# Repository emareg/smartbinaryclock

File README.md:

# smartbinaryclock
binary clock with several sensors

### Features:
* hour, minute, second
* day, month, year
* alarm clock

### Sensors:
* temperature
* brightness
* (barometer)

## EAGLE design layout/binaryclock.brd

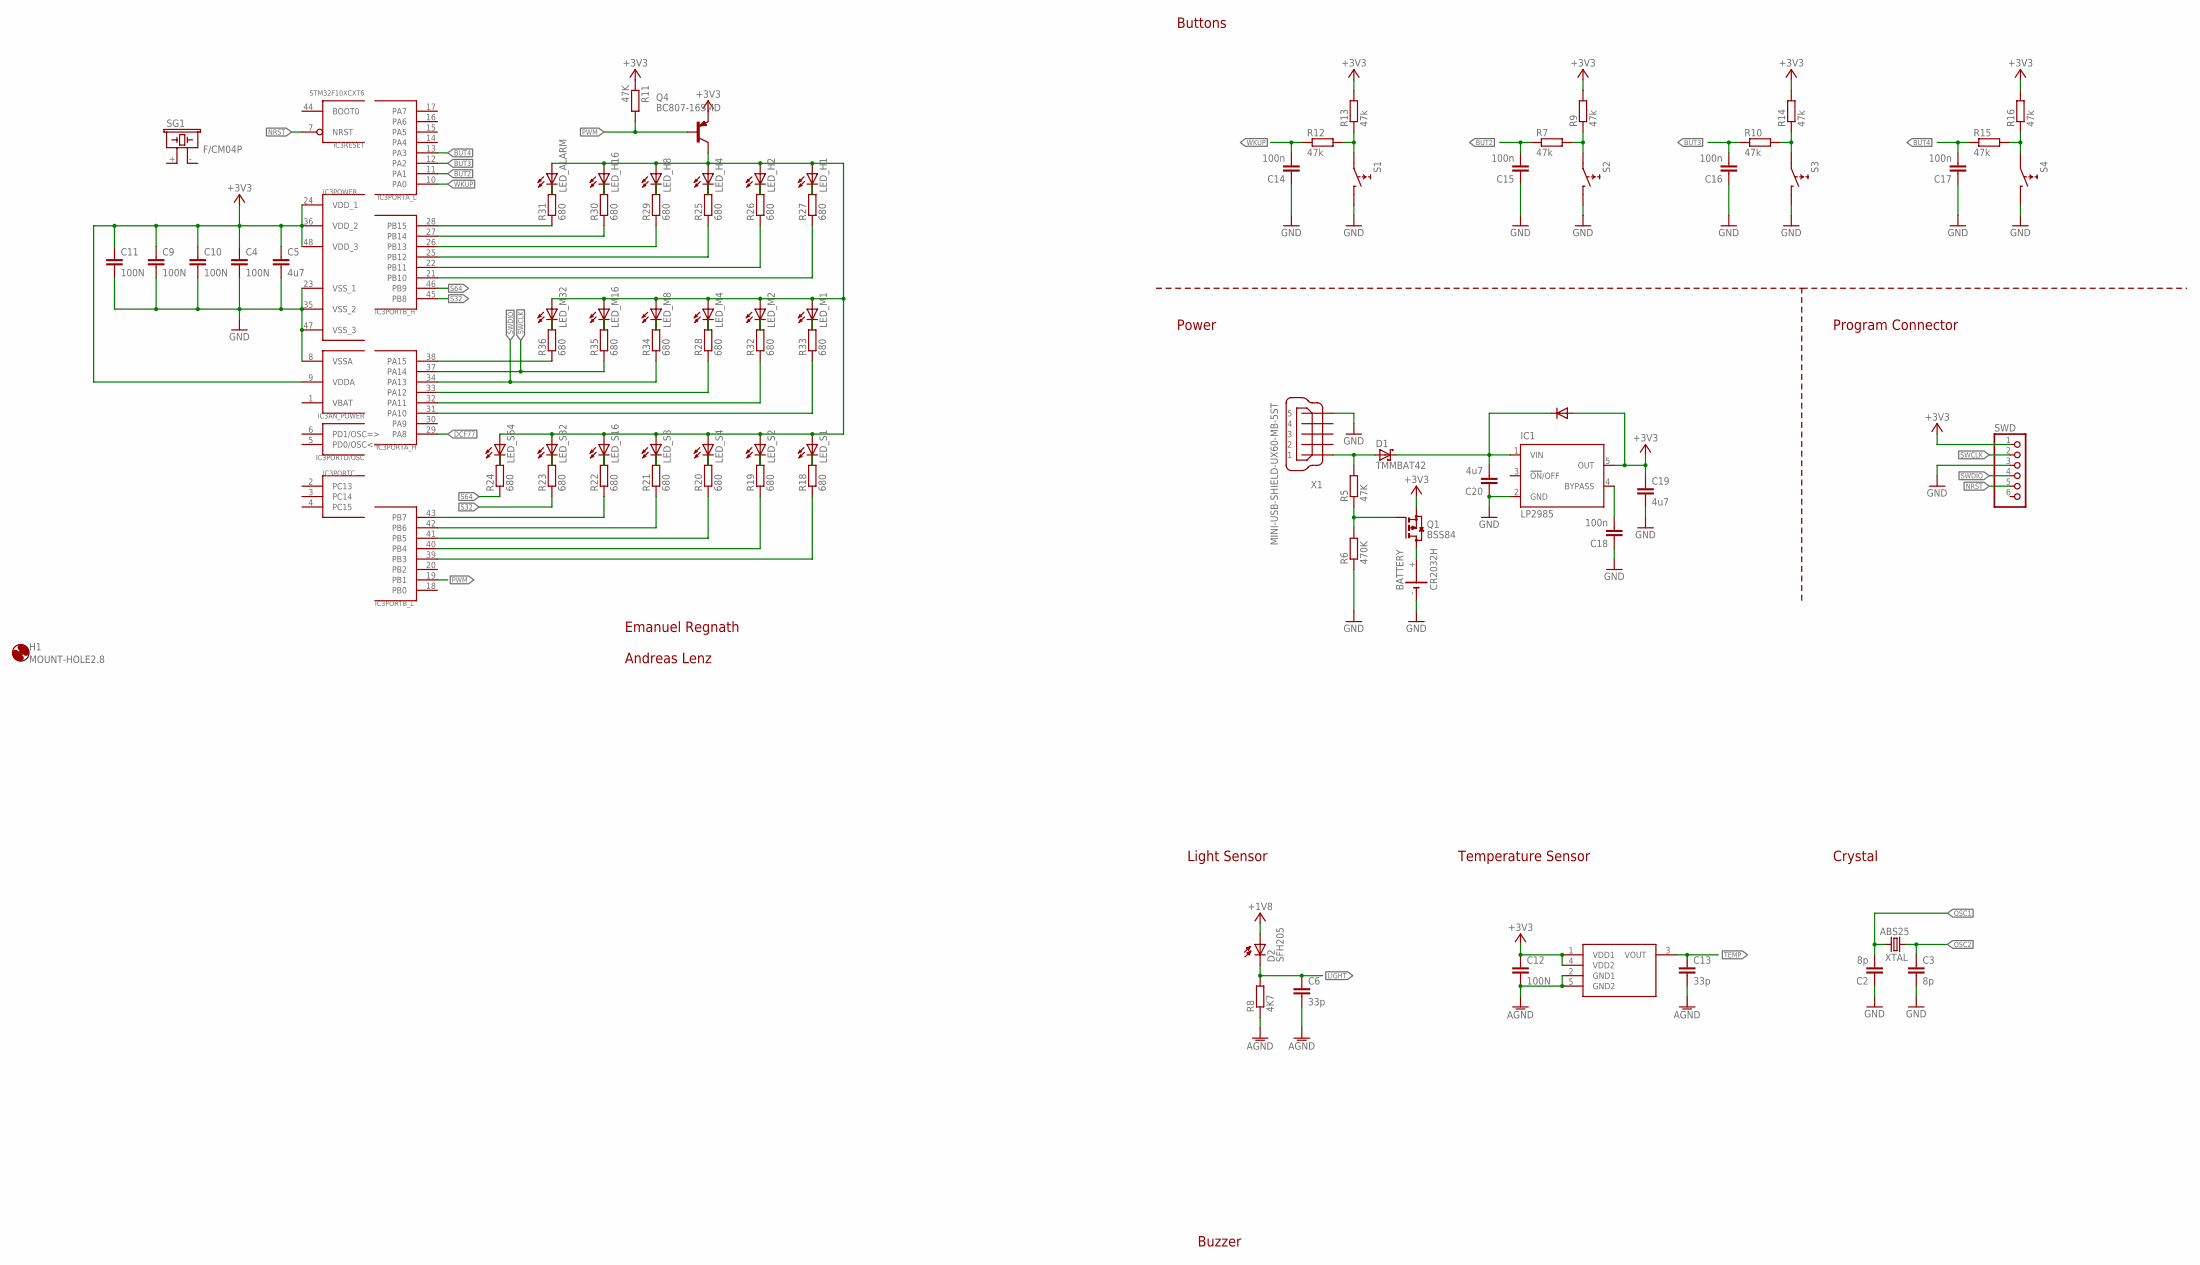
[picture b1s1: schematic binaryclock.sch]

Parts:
BATTERY: CR2032H
BLA: LMT85; DCK_R-PDSO-G5
C2, C3: 8p; C0805K
C4, C9, C10, C11, C12: 100N; C0603
C5, C19, C20: 4u7; C0805
C6, C13: 33p; C0603
C14, C15, C16, C17, C18: 100n; C0603K
D1: TMMBAT42; SOD80
D2: SFH205
H1: MOUNT-HOLE2.8; 2,8
IC1: LP2985; SOT23-5
IC3: STM32F10XCXT6; TQFP48
LED_ALARM: LEDSML0603; SML0603
LED_H1, LED_H2, LED_H4, LED_H8, LED_H16: LEDSML0603; SML0603
LED_M1, LED_M2, LED_M4, LED_M8, LED_M16, LED_M32: LEDSML0603; SML0603
LED_S1, LED_S2, LED_S4, LED_S8, LED_S16, LED_S32, LED_S64: LEDSML0603; SML0603
Q1: BSS84; SOT23
Q4: BC807-16SMD; SOT23-BEC
R5, R11: 47K; R0805
R6: 470K; R0805
R7, R9, R10, R12, R13, R14, R15, R16: 47k; M2012
R8: 4K7; R0603
R18, R19, R20, R21, R22, R23, R24, R25, R26, R27, R28, R29, R30, R31, R32, R33, R34, R35, R36: 680; R0603
S1, S2, S3, S4: SWITCH1
SG1: F/CM04P
SWD: PINHD-1X6; 1X06
X1: MINI-USB-SHIELD-UX60-MB-5ST; UX60-MB-5ST
XTAL: ABS25

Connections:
+1V8: D2.A
+3V3: BLA.1 (VDD1), BLA.4 (VDD2), C4.1, C5.1, C9.1, C10.1, C11.1, C12.1, C19.1, IC1.5 (OUT), IC3.9 (VDDA), IC3.24 (VDD_1), IC3.36 (VDD_2), IC3.48 (VDD_3), Q1.2 (S), Q4.E, R9.2, R11.1, R13.2, R14.2, R16.2, SWD.1
AGND: BLA.2 (GND1), BLA.5 (GND2), C6.2, C12.2, C13.2, R8.1
BUT2: C15.2, IC3.11 (PA1), R7.1
BUT3: C16.2, IC3.12 (PA2), R10.1
BUT4: C17.2, IC3.13 (PA3), R15.1
DCF77: IC3.29 (PA8)
GND: BATTERY.-, C2.1, C3.2, C4.2, C5.2, C9.2, C10.2, C11.2, C14.1, C15.1, C16.1, C17.1, C18.1, C19.2, C20.1, IC1.2 (GND), IC3.8 (VSSA), IC3.23 (VSS_1), IC3.35 (VSS_2), IC3.47 (VSS_3), R6.1, S1.P$2 (1), S2.P$2 (1), S3.P$2 (1), S4.P$2 (1), SWD.3, X1.5
LIGHT: C6.1, D2.K (C), R8.2
unnamed: BATTERY.+, Q1.3 (D)
unnamed: Q1.1 (G), R5.1, R6.2
unnamed: C20.2, D1.1 (C), IC1.1 (VIN)
unnamed: R12.2, R13.1, S1.P$1 (0)
unnamed: D1.2 (A), R5.2, X1.1
unnamed: IC3.38 (PA15), R36.1
unnamed: IC3.39 (PB3), R18.1
unnamed: LED_ALARM.A, LED_H1.A, LED_H2.A, LED_H4.A, LED_H8.A, LED_H16.A, LED_M1.A, LED_M2.A, LED_M4.A, LED_M8.A, LED_M16.A, LED_M32.A, LED_S1.A, LED_S2.A, LED_S4.A, LED_S8.A, LED_S16.A, LED_S32.A, LED_S64.A, Q4.C
unnamed: R7.2, R9.1, S2.P$1 (0)
unnamed: R10.2, R14.1, S3.P$1 (0)
unnamed: R15.2, R16.1, S4.P$1 (0)
unnamed: C18.2, IC1.4 (BYPASS)
unnamed: LED_M8.C, R34.2
unnamed: LED_S1.C, R18.2
unnamed: IC3.40 (PB4), R19.1
unnamed: LED_S8.C, R21.2
unnamed: IC3.41 (PB5), R20.1
unnamed: IC3.42 (PB6), R21.1
unnamed: LED_H8.C, R29.2
unnamed: LED_S2.C, R19.2
unnamed: LED_S4.C, R20.2
unnamed: IC3.33 (PA12), R28.1
unnamed: IC3.32 (PA11), R32.1
unnamed: IC3.31 (PA10), R33.1
unnamed: LED_H4.C, R25.2
unnamed: LED_S16.C, R22.2
unnamed: LED_S32.C, R23.2
unnamed: LED_S64.C, R24.2
unnamed: IC3.43 (PB7), R22.1
unnamed: IC3.28 (PB15), R31.1
unnamed: IC3.27 (PB14), R30.1
unnamed: LED_H2.C, R26.2
unnamed: LED_H1.C, R27.2
unnamed: LED_H16.C, R30.2
unnamed: LED_ALARM.C, R31.2
unnamed: LED_M4.C, R28.2
unnamed: LED_M2.C, R32.2
unnamed: LED_M1.C, R33.2
unnamed: LED_M16.C, R35.2
unnamed: LED_M32.C, R36.2
unnamed: IC3.26 (PB13), R29.1
unnamed: IC3.25 (PB12), R25.1
unnamed: IC3.22 (PB11), R26.1
unnamed: IC3.21 (PB10), R27.1
NRST: IC3.7 (NRST), SWD.5
OSC1: C2.2, XTAL.1
OSC2: C3.1, XTAL.4 (2)
PWM: IC3.19 (PB1), Q4.B, R11.2
S32: IC3.45 (PB8), R23.1
S64: IC3.46 (PB9), R24.1
SWCLK: IC3.37 (PA14), R35.1, SWD.2
SWDIO: IC3.34 (PA13), R34.1, SWD.4
TEMP: BLA.3 (VOUT), C13.1
VBAT: IC3.1 (VBAT)
WKUP: C14.2, IC3.10 (PA0), R12.1

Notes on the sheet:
Buttons
Power
Program Connector
Light Sensor
Temperature Sensor
Crystal
Buzzer

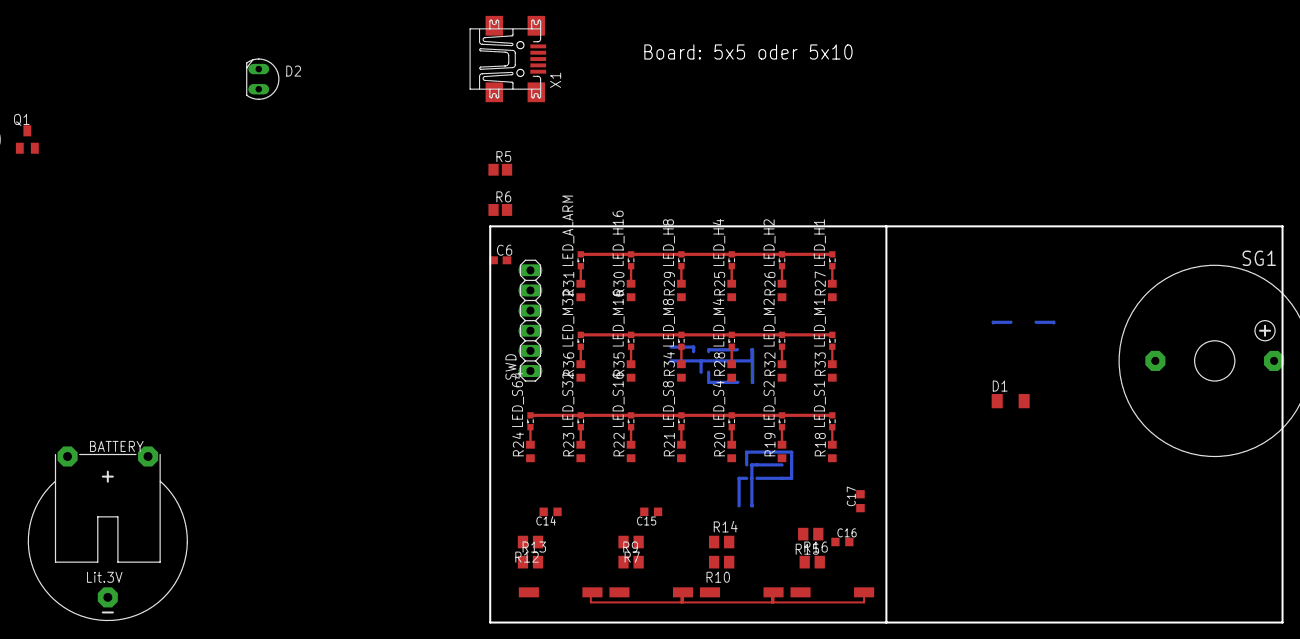
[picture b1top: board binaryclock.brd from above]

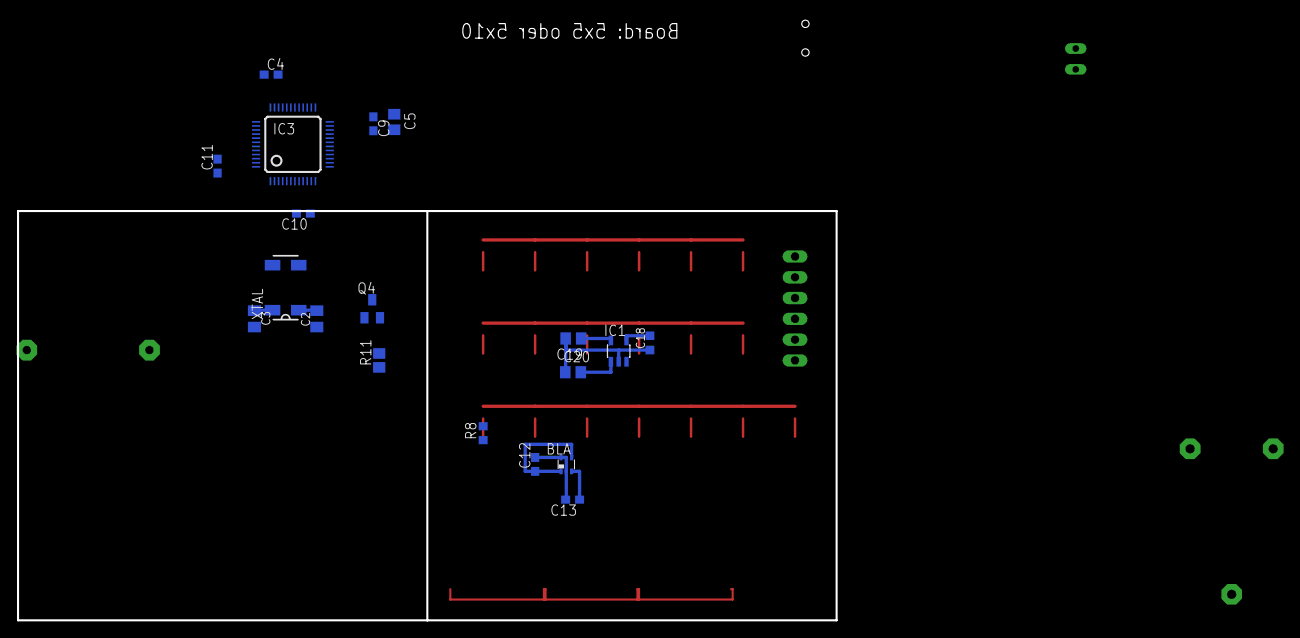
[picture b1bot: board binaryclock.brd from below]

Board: 2 copper layers, 100.0 x 50.0 mm, 84 parts (19 on the bottom side), 61 nets.

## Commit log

2015-03-21 added eagle layout
2015-03-21 added description
2015-03-30 split layout into three frames
2020-02-18 initial commit for version 3
2020-03-29 fix summertime update on startup
